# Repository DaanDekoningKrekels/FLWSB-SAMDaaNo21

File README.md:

# Flexible LoRaWAN Sensor Board SAMDaaNo21

Het FLWSB Main Board is een microcontroller bord gebaseerd op de ATSAM D21 in de vormfactor vergelijkbaar met een Arduino Nano. Het moet gemakkelijk zijn om dit bord in een breadboard te prikken en zo testen uit te voeren of schakelingen te bouwen. 

[PDF versie van de pinout diagram](./assets/SAMDaaNo21-pinout.pdf ':ignore')

## KiCad bibliotheken

Het is handig om een printplaat te kunnen ontwikkelen waar de SAMDaaNo21 opgeprikt kan worden.

Om dit proces te vergemakkelijken is er een KiCad bibliotheek ontwikkeld, die bevat een symbol, footprint en 3D-model.

Het is aangeraden om bibliotheken die niet standaard in KiCad zitten mee in de projectmap te steken en te importeren als projectbibliotheek. Als je je projectmap dan deelt met derden zullen zij meteen beschikken over alle nodige bibliotheken.

Tutorial: [How to import into KiCad V6 & later?](https://support.snapeda.com/en/articles/5995733-how-to-import-into-kicad-v6-later)

[SAMDaaNo21 bibliotheek bestanden](https://github.com/Dacetylan/FLWSB/tree/SAMDaaNo21/src/printed-circuit-boards/FLWSB-SAMDaaNo21-KiCad-lib)

## Schema

Het elektrisch schema van dit bord ziet er als volgt uit:

Alle onderdelen worden verder toegelicht.

[ATSAM D21 Datasheet](https://ww1.microchip.com/downloads/en/DeviceDoc/SAM-D21DA1-Family-Data-Sheet-DS40001882G.pdf)

## Testpunten

Er zijn verschillende testpunten toegevoegd om op een gemakkelijke en toegankelijke manier verschillende parameters op het bord te kunnen meten.

Er is gekozen voor through hole testpunten zodat het gemakkelijk is om deze met een probe te meten. Alle testpunten zijn te vinden nabij de USB poort.

| Testpunt nummer | Verbinding                                                   |
| --------------- | ------------------------------------------------------------ |
| TP1             | VBUS: 5 V afkomstig van USB                                  |
| TP2             | VDD: 3,3 V gereguleerde spanning                              |
| TP3             | VIN: Ingangsspanning voordat het naar de lineaire regelaar gaat |

## LoRaWAN Module

Er is een RN2483 module mee geïmplementeerd op de printplaat. Deze is aangesloten op de UART bus van SERCOM 2.

De RN2483 bevindt zich aan het uiteinde. Er kan een antenne aangesloten worden via een U.FL connector.  

[Productpagina connector](https://be.farnell.com/hirose-hrs/u-fl-r-smt-1-10/rf-coaxial-u-fl-straight-jack/dp/1688077)

## USB Interface & VIN

Het schema voor de USB-interface is gebaseerd op een voorbeeld uit een Atmel handleiding. De zener diodes die zichtbaar zijn zorgen ervoor dat de kans op schade door elektrostatische ontlading (ESD) beperkt wordt.

[Ref USB-applications note](https://ww1.microchip.com/downloads/en/DeviceDoc/Atmel-42261-SAM-D21-USB_Application-Note_AT06475.pdf)

[Ref schematic checklist](https://ww1.microchip.com/downloads/en/DeviceDoc/SAM-D21DA1-Family-Data-Sheet-DS40001882G.pdf#_OPENTOPIC_TOC_PROCESSING_d10240e380866)

De Schottky diode (D6) is er om de USB-poort van je laptop te beschermen wanneer het bord van stroom wordt voorzien via de VIN pin. Het zou kunnen dat aan de VIN pin een hogere spanning wordt geleverd dan 5 V waardoor dit potentiaalverschil ongewenste stroom kan laten vloeien. Hetzelfde principe wordt toegepast bij de ESP32 DEVKIT.

`TP3` is een testpunt dat aanwezig is om op een toegankelijke manier de VIN-spanning te meten.

[Ref ESP32 schema](https://dl.espressif.com/dl/schematics/esp32_devkitc_v4-sch-20180607a.pdf)

Het bordje kan voorzien worden van stroom via de USB-C poort. Een LDO (Low Dropout regelaar) zal de spanning afkomstig van de computer reguleren naar een stabiele 3,3 V.

De LDO is een LD1117S33 en ondersteunt een minimale ingangsspanning van 4,3 V en een maximale van 15 V. Dat kan worden aangelegd via de VIN pin. Er is een Schottky diode voorzien om ervoor te zorgen dat de spanning van VIN niet op de USB poort komt te staan.

*Let op dat je met een lineaire regelaar te maken hebt. Hoe hoger de ingangsspanning, hoe warmer de LDO zal worden!*

Het is ook mogelijk om de regelaar over te slaan en rechtstreeks 3,3 V te leveren via de 3V3 pin. Dit kan handig zijn bij een situatie waarin we zo zuinig mogelijk willen zijn en een efficiëntere 3,3 V regelaar gebruiken van een andere pcb. *Belangrijk is dat deze spanning niet te hard mag afwijken van 3,3 V!*

## RESET & DEBUG

De reset knop is opgebouwd zoals in de datasheet van de ATSAM D21 wordt weergegeven onder "Schematic Checklist Figure 45-4. External Reset Circuit Schematic".

Als er nog geen bootloader op de ATSAMD staat of als we een bare metal installatie gebruiken zullen we gebruik moeten maken van de program en debug header. Dat zijn de 3 pinnen centraal op de printplaat voor de LoRaWAN module. De pinout van links naar recht is: RESET, SWDIO, SWCLK. 

De ATSAMD maakt gebruik van Serial Wire Debugging (SWD), dat maakt het mogelijk om via fuses in te stellen, binaries in te laden en zelfs break-points aan je code toe te voegen.

## Low Dropout Lineair Regulator

In dit geval wordt er een LD1117 3,3 V regelaar gebruikt. Deze regelaar kan met een vrij groot ingangsbereik (tot 15 V) een uitgangsspanning van 3,3 V leveren.

`TP2` is een testpunt dat aanwezig is om op een toegankelijke manier de 3.3 V gereguleerde spanning te meten.

[LD1117 datasheet](https://www.st.com/resource/en/datasheet/ld1117.pdf)

## Power Supply Connections

Het schema voor de ontkoppelcondensatoren en spoel voor de ATSAM D21 komt ook rechtstreeks uit de datasheet. Wat belangrijk is bij deze componenten is dat alles rechts van de blauwe stippellijn zo dicht mogelijk bij de vermelde pinnen staat. Deze condensatoren vangen kleine storingen en rimpels op die zich voordoen in de bronspanning.

## Input / Output

Dit zijn alle GPIO, SERCOM en power aansluitingen die via pinheaders naar buiten worden gebracht. De SERCOM poorten zijn alvast gedefinieerd zodat onder andere de pull-up weerstanden geplaatst kunnen worden. Alle andere poorten zijn voor algemeen gebruik. In de datasheet van de ATSAM D21 onder 7. I/O Multiplexing and Considerations kunnen alle verschillende mogelijkheden van deze aansluitingen gevonden worden (AC, ADC, DAC, PTC, DAC, IO, ...).

PA12 en PA13 zijn onderdeel van de I²C bus en hebben al een pull-up weerstand van 4,7 K voorzien. *Bij het plaatsen van nog externe pull-up weerstanden zullen zij in parallel staan en zal de weerstandswaarde te laag worden.*

| I/O Pin | Pin      | SERCOM                  | SERCOM-ALT       | External Interrupt | ADC, DAC, AC, REF    | Peripheral Touch Controller | TC/TCC         | TCC            | COM               | Generic Clock Generator |
| ------- | -------- | ----------------------- | ---------------- | ------------------ | -------------------- | --------------------------- | -------------- | -------------- | ----------------- | ----------------------- |
| GND     | PowerPin | Ground Reference        |                  |                    |                      |                             |                |                |                   |                         |
| PA02    | 3        |                         |                  | EXTINT:2           | ADC:0<br/>VOUT       | Y:0                         |                | TCC3/<br/>WO:0 |                   |                         |
| PA03    | 4        |                         |                  | EXTINT:3           | ADC:1<br/>VREFA      | Y:1                         |                | TCC3/<br/>WO:1 |                   |                         |
| PB08    | 7        |                         | SCOM4/<br/>PAD:0 | EXTINT:8           | ADC:2                | Y:14                        | TC4/<br/>WO:0  | TCC3/<br/>WO:6 |                   |                         |
| PB09    | 8        |                         | SCOM4/<br/>PAD:1 | EXTINT:9           | ADC:3                | Y:15                        | TC4/<br/>WO:1  | TCC3/<br/>WO:7 |                   |                         |
| PA04    | 9        |                         | SCOM0/<br/>PAD:0 | EXTINT:4           | ADC:4<br/>AC:0 VREFB | Y:2                         | TCC0/<br/>WO:0 | TCC3/<br/>WO:2 |                   |                         |
| PA05    | 10       |                         | SCOM0/<br/>PAD:1 | EXTINT:5           | ADC:5<br/>AC:1       | Y:3                         | TCC0/<br/>WO:1 | TCC3/<br/>WO:3 |                   |                         |
| PA06    | 11       |                         | SCOM0/<br/>PAD:2 | EXTINT:6           | ADC:6<br/>AC:2       | Y:4                         | TCC1/<br/>WO:0 | TCC3/<br/>WO:4 |                   |                         |
| PA07    | 12       |                         | SCOM0/<br/>PAD:3 | EXTINT:7           | ADC:7<br/>AC:3       | Y:5                         | TCC1/<br/>WO:1 | TCC3/<br/>WO:5 | I2S/<br/>SD:0     |                         |
| PA08    | 13       | SCOM0/<br/>PAD:0        | SCOM2/<br/>PAD:0 | NMI                | ADC:16               | X:0                         | TCC0/<br/>WO:0 | TCC1/<br/>WO:2 | I2S/<br/>SD:1     |                         |
| PA09    | 14       | SCOM0/<br/>PAD:1        | SCOM2/<br/>PAD:1 | EXTINT:9           | ADC:17               | X:1                         | TCC0/<br/>WO:1 | TCC1/<br/>WO:3 | I2S/<br/>MCK:0    |                         |
| PA10    | 15       | SCOM0/<br/>PAD:2        | SCOM2/<br/>PAD:2 | EXTINT:10          | ADC:18               | X:2                         | TCC1/<br/>WO:0 | TCC0/<br/>WO:2 | I2S/<br/>SCK:0    | GCLK:4                  |
| PA11    | 16       | SCOM0/<br/>PAD:3        | SCOM2/<br/>PAD:3 | EXTINT:11          | ADC:19               | X:3                         | TCC1/<br/>WO:1 | TCC0/<br/>WO:3 | I2S/<br/>FS:0     | GCLK:5                  |
| PA12    | 21       | SCOM2/<br/>PAD:0        | SCOM4/<br/>PAD:0 | EXTINT:12          | AC:0                 |                             | TCC2/<br/>WO:0 | TCC0/<br/>WO:6 |                   |                         |
| PA13    | 22       | SCOM2/<br/>PAD:1        | SCOM4/<br/>PAD:1 | EXTINT:13          | AC:1                 |                             | TCC2/<br/>WO:1 | TCC0/<br/>WO:7 |                   |                         |
| VIN     | PowerPin | LDL1117S33 4.3 V - 15 V |                  |                    |                      |                             |                |                |                   |                         |
| 3V3     | PowerPin | 3.3V LDO output         |                  |                    |                      |                             |                |                |                   |                         |
| GND     | PowerPin | Ground Reference        |                  |                    |                      |                             |                |                |                   |                         |
| PB03    | 48       |                         | SCOM5/<br/>PAD:1 | EXTINT:3           | ADC:11               | Y:9                         | TC6/<br/>WO:1  | TCC3/<br/>WO:3 |                   |                         |
| PB22    | 37       |                         | SCOM5/<br/>PAD:2 | EXTINT:6           |                      |                             | TC7/<br/>WO:0  | TCC3/<br/>WO:0 |                   | GCLK:0                  |
| PA23    | 32       | SCOM3/<br/>PAD:1        | SCOM5/<br/>PAD:1 | EXTINT:7           |                      | X:11                        | TC4/<br/>WO:0  | TCC0/<br/>WO:5 | USB/<br/>SOF 1KhZ | GCLK:7                  |
| PA22    | 31       | SCOM3/<br/>PAD:0        | SCOM5/<br/>PAD:0 | EXTINT:6           |                      | X:10                        | TC4/<br/>WO:1  | TCC0/<br/>WO:4 |                   | GCLK:6                  |
| PA21    | 30       | SCOM5/<br/>PAD:3        | SCOM3/<br/>PAD:3 | EXTINT:5           |                      | X:9                         | TC7/<br/>WO:1  | TCC0/<br/>WO:7 | I2S/<br/>FS:0     | GCLK:5                  |
| PA20    | 29       | SCOM5/<br/>PAD:2        | SCOM3/<br/>PAD:2 | EXTINT:4           |                      | X:8                         | TC7/<br/>WO:0  | TCC0/<br/>WO:6 | I2S/<br/>SCK:0    | GCLK:4                  |
| PA19    | 28       | SCOM1/<br/>PAD:3        | SCOM3/<br/>PAD:3 | EXTINT:3           | AC:1                 | X:7                         | TC3/<br/>WO:1  | TCC0/<br/>WO:3 | I2S/<br/>SD:0     |                         |
| PA18    | 27       | SCOM1/<br/>PAD:2        | SCOM3/<br/>PAD:2 | EXTINT:2           | AC:0                 | X:6                         | TC3/<br/>WO:0  | TCC0/<br/>WO:2 |                   |                         |
| PA17    | 26       | SCOM1/<br/>PAD:1        | SCOM3/<br/>PAD:1 | EXTINT:1           |                      | X:5                         | TCC2/<br/>WO:1 | TCC0/<br/>WO:7 |                   | GCLK:3                  |
| PA16    | 25       | SCOM1/<br/>PAD:0        | SCOM3/<br/>PAD:0 | EXTINT:0           |                      | X:4                         | TCC2/<br/>WO:0 | TCC0/<br/>WO:6 |                   | GCLK:2                  |
| PA15    | 24       | SCOM2/<br/>PAD:3        | SCOM4/<br/>PAD:3 | EXTINT:15          |                      |                             | TC3/<br/>WO:1  | TCC0/<br/>WO:5 |                   | GCLK:1                  |
| PA14    | 23       | SCOM2/<br/>PAD:2        | SCOM4/<br/>PAD:2 | EXTINT:14          |                      |                             | TC3/<br/>WO:0  | TCC0/<br/>WO:4 |                   | GCLK:0                  |

### Legende

`SERCOM`: Serial Communication, keuze tussen: USART, I²C, SPI of SMBus

`EXTINT[n]`: External Interrupts

`AIN[n]`: ADC Analog Inputs

`X[n]`, `Y[n]`: Peripheral Touch Controller - PTC Input

`TC4/WO[n]`, `TC6/WO[n]`: Waveform/PWM Outputs

`TCC3/WO[n]`: Waveform/PWM Outputs/ Capture Inputs

`AC/CMP[n]`: AC Comparator Outputs

`I2S/FS[n]`: Inter-IC Sound Controller, I²S Word Select or TDM Frame Sync

`GCLK_IO[n]`: Generic Clock (source clock or generic clock generator output)

## Toekomstige verbeteringen

- Momenteel zijn er geen mounting holes aanwezig, dat vonden we  nog niet prioritair.
  - Mouning holes of inkepingen aan de randen van de printplaat zijn dus nog mogelijk en kunnen ook zeker van pas komen.
- De impedantie van het pad naar de antenne-aansluiting is niet theoretisch berekend. Dit is iets waar in een volgende versie over kan worden nagedacht.
- Er is geen LED aanwezig.
- Op het silkscreen staat een fout, `PA07` staat op het silkscreen als `PA09`. 
- Het schema bevat een fout die de LoRaWAN module onbruikbaar maakt. RX en TX van de UART-verbinding moeten omgewisseld worden.
  
### Tijdelijke oplossing LoRaWAN module

Een UART-verbinding heeft een TX (transmit) en RX (receive) aansluiting nodig. Logischerwijze zal je dus, bij een verbinding tussen twee apparaten, RX en TX met elkaar verbinden. Bij het ontwerpen van dit schema is door onoplettendheid TX met TX verbonden en RX met RX verbonden.

De PINMUX van de ATSAM D21 kan iedere SERCOM pin als RX instellen, maar niet iedere pin als TX schakelen. Dit maakt het onmogelijk om de oplossing geheel softwarematig te zoeken. Enkel PAD0 en PAD2 van een SERCOM poort kan je instellen als TX.

Wij hebben `PA8` (`S2TX` op het silkscreen) ingesteld als RX omdat deze verbonden is met de TX van de LoRaWAN module. `PA09` (`S2RX` op het silkscreen) hebben we hoog impedant gezet (`INPUT`) en kortgesloten met `PA10`. `PA10` is PAD2 van SERCOM2 dus kan ingesteld worden als nieuwe TX.

Het resultaat is dat we nu het baantje naar de RESET pin van de LoRaWAN module moeten onderbreken, omdat `PA10` verbonden is met deze pin. Die onderbreking is het gemakkelijkste te maken met een mesje of platte schroevendraaier net op de plek waar deze richting het pad van de module gaat.

De aanpassingen van deze pinnen is gemaakt in de ArduinoCore dus er hoeft in de code niets gewijzigd te worden.

Er is geen manier meer om de module te resetten vanaf de MCU, moest dat nodig zijn, dan kan er een kabeltje gesoldeerd worden naar een van de vrije GPIO pinnen.

## Bill of Materials

[Bill of materials ibom](./bom/ibom.html ':include :type=iframe width=100% height=1024px')

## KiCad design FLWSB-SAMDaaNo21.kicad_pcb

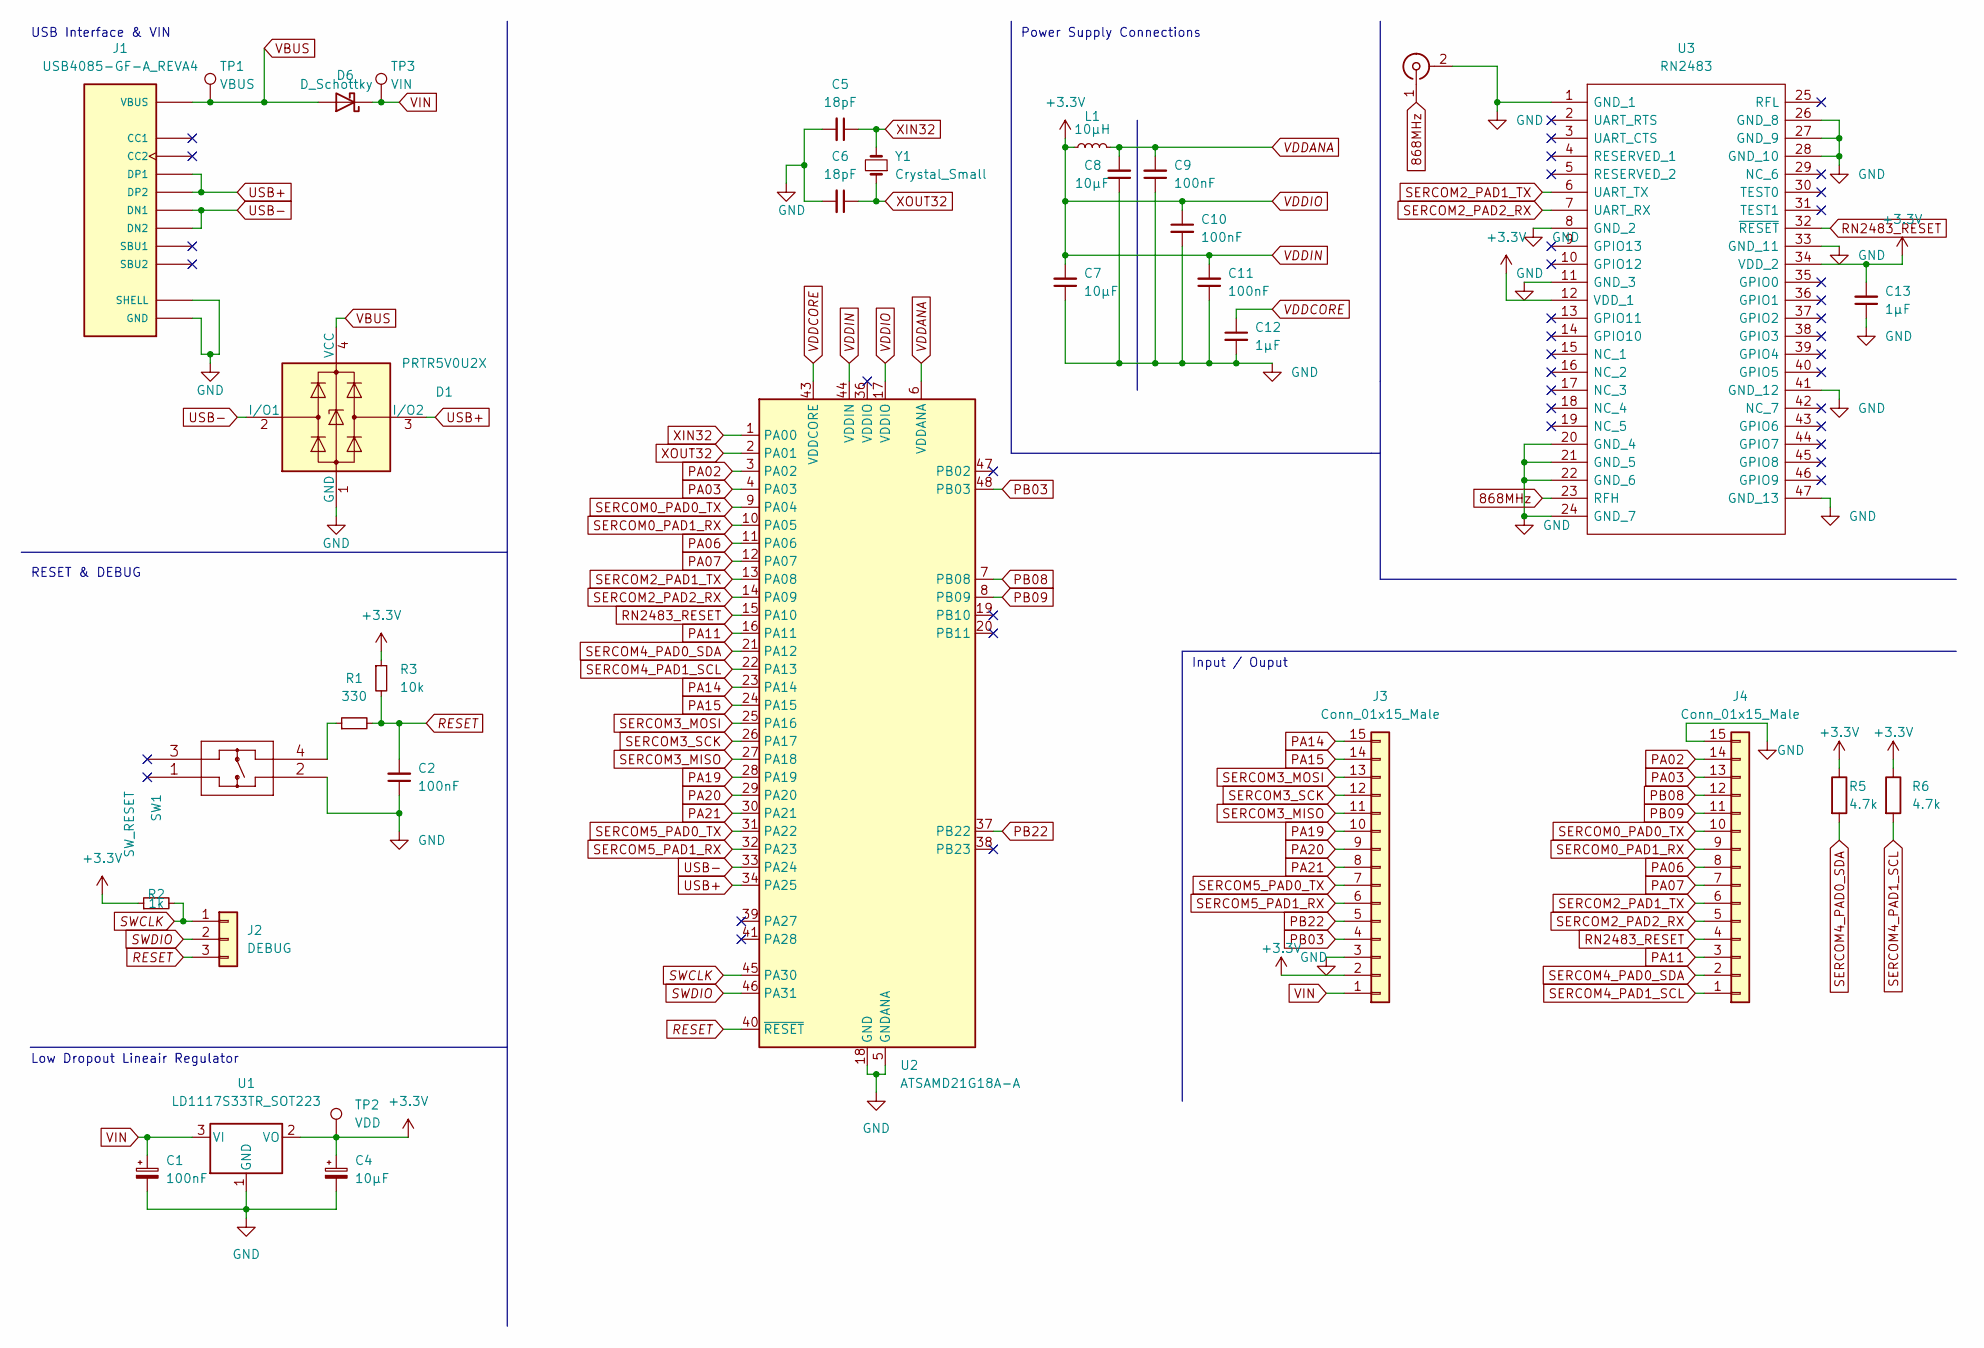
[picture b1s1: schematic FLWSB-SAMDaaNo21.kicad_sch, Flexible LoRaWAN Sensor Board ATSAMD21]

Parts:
C1, C2, C9, C10, C11: 100nF; C_0805_2012Metric_Pad1.18x1.45mm_HandSolder
C4, C7, C8: 10µF; C_0805_2012Metric_Pad1.18x1.45mm_HandSolder
C5, C6: 18pF; C_0805_2012Metric_Pad1.18x1.45mm_HandSolder
C12, C13: 1µF; C_0805_2012Metric_Pad1.18x1.45mm_HandSolder
D1: PRTR5V0U2X; SOT-143
D6: D_Schottky; SOD-123FL
J1: USB4085-GF-A_REVA4; GCT_USB4085-GF-A_REVA4; PARTREV A4
J2: DEBUG; PinHeader_1x03_P2.54mm_Vertical
J3, J4: Conn_01x15_Male; PinHeader_1x15_P2.54mm_Vertical
J6: Conn_Coaxial; U.FL_Molex_MCRF_73412-0110_Vertical
L1: 10µH; L_Murata_LQH2MCNxxxx02_2.0x1.6mm
R1: 330; R_0805_2012Metric_Pad1.20x1.40mm_HandSolder
R2: 1k; R_0805_2012Metric_Pad1.20x1.40mm_HandSolder
R3: 10k; R_0805_2012Metric_Pad1.20x1.40mm_HandSolder
R5, R6: 4.7k; R_0805_2012Metric_Pad1.20x1.40mm_HandSolder
SW1: SW_RESET; KMR7_CNK
TP1: VBUS; TestPoint_THTPad_1.0x1.0mm_Drill0.5mm
TP2: VDD; TestPoint_THTPad_1.0x1.0mm_Drill0.5mm
TP3: VIN; TestPoint_THTPad_1.0x1.0mm_Drill0.5mm
U1: LD1117S33TR_SOT223; SOT-223-3_TabPin2
U2: ATSAMD21G18A-A; TQFP-48_7x7mm_P0.5mm
U3: RN2483; Manufacturer_Part_Number RN2483
Y1: Crystal_Small; Crystal_SMD_3215-2Pin_3.2x1.5mm

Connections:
868MHz: J6.1 (In), U3.23 (RFH)
GND: C1.2, C2.1, C4.2, C5.2, C6.2, C7.1, C8.1, C9.1, C10.2, C11.1, C12.2, C13.1, D1.1 (GND), J1.A1 (GND), J1.A12 (GND), J1.B1 (GND), J1.B12 (GND), J1.P1 (SHELL), J1.P2 (SHELL), J1.P3 (SHELL), J1.P4 (SHELL), J3.3, J4.15, J6.2 (Ext), SW1.2, U1.1 (GND), U2.5 (GNDANA), U2.18 (GND), U2.35 (GND), U2.42 (GND), U3.1 (GND_1), U3.8 (GND_2), U3.11 (GND_3), U3.20 (GND_4), U3.21 (GND_5), U3.22 (GND_6), U3.24 (GND_7), U3.26 (GND_8), U3.27 (GND_9), U3.28 (GND_10), U3.33 (GND_11), U3.41 (GND_12), U3.47 (GND_13); also elsewhere on the board
unnamed: R1.1, SW1.4
PA02: J4.14, U2.3 (PA02)
PA03: J4.13, U2.4 (PA03)
PA06: J4.8, U2.11 (PA06)
PA07: J4.7, U2.12 (PA07)
PA11: J4.3, U2.16 (PA11)
PA14: J3.15, U2.23 (PA14)
PA15: J3.14, U2.24 (PA15)
PA19: J3.10, U2.28 (PA19)
PA20: J3.9, U2.29 (PA20)
PA21: J3.8, U2.30 (PA21)
PB03: J3.4, U2.48 (PB03)
PB08: J4.12, U2.7 (PB08)
PB09: J4.11, U2.8 (PB09)
PB22: J3.5, U2.37 (PB22)
RESET: C2.2, J2.3, R1.2, R3.2, U2.40 (~RESET)
RN2483_RESET: J4.4, U2.15 (PA10), U3.32 (~RESET)
SERCOM0_PAD0_TX: J4.10, U2.9 (PA04)
SERCOM0_PAD1_RX: J4.9, U2.10 (PA05)
SERCOM2_PAD1_TX: J4.6, U2.13 (PA08), U3.6 (UART_TX)
SERCOM2_PAD2_RX: J4.5, U2.14 (PA09), U3.7 (UART_RX)
SERCOM3_MISO: J3.11, U2.27 (PA18)
SERCOM3_MOSI: J3.13, U2.25 (PA16)
SERCOM3_SCK: J3.12, U2.26 (PA17)
SERCOM4_PAD0_SDA: J4.2, R5.2, U2.21 (PA12)
SERCOM4_PAD1_SCL: J4.1, R6.2, U2.22 (PA13)
SERCOM5_PAD0_TX: J3.7, U2.31 (PA22)
SERCOM5_PAD1_RX: J3.6, U2.32 (PA23)
SWCLK: J2.1, R2.2, U2.45 (PA30)
SWDIO: J2.2, U2.46 (PA31)
USB+: D1.3 (I/O2), J1.A6 (DP1), J1.B6 (DP2), U2.34 (PA25)
USB-: D1.2 (I/O1), J1.A7 (DN1), J1.B7 (DN2), U2.33 (PA24)
VBUS: D1.4 (VCC), D6.2 (A), J1.A4 (VBUS), J1.A9 (VBUS), J1.B4 (VBUS), J1.B9 (VBUS), TP1.1
VDDANA: C8.2, C9.2, L1.2, U2.6 (VDDANA)
VDDCORE: C12.1, U2.43 (VDDCORE)
VDDIN: C4.1, C7.2, C10.1, C11.2, C13.2, J3.2, L1.1, R2.1, R3.1, R5.1, R6.1, TP2.1, U1.2 (VO), U2.17 (VDDIO), U2.44 (VDDIN), U3.12 (VDD_1), U3.34 (VDD_2)
VIN: C1.1, D6.1 (K), J3.1, TP3.1, U1.3 (VI)
XIN32: C5.1, U2.1 (PA00), Y1.2; also elsewhere on the board
XOUT32: C6.1, U2.2 (PA01), Y1.1

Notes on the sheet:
Power Supply Connections
Input / Ouput
Low Dropout Lineair Regulator
RESET & DEBUG
USB Interface & VIN

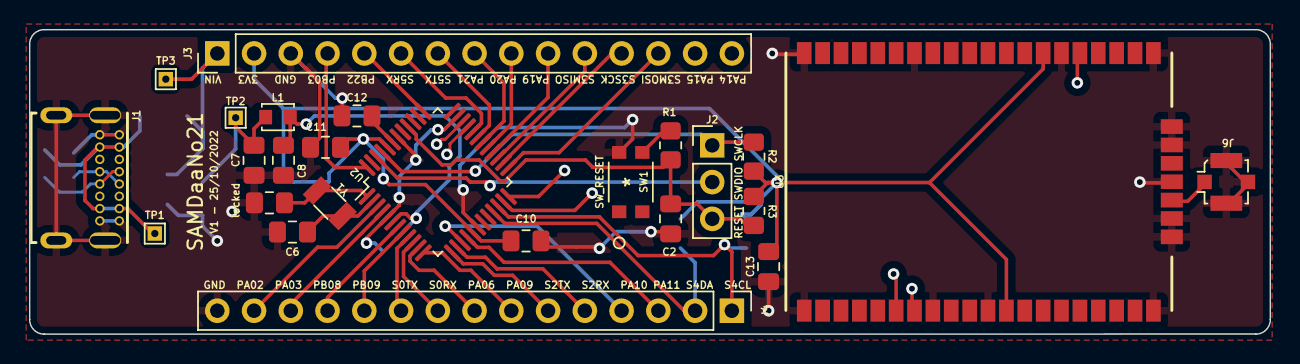
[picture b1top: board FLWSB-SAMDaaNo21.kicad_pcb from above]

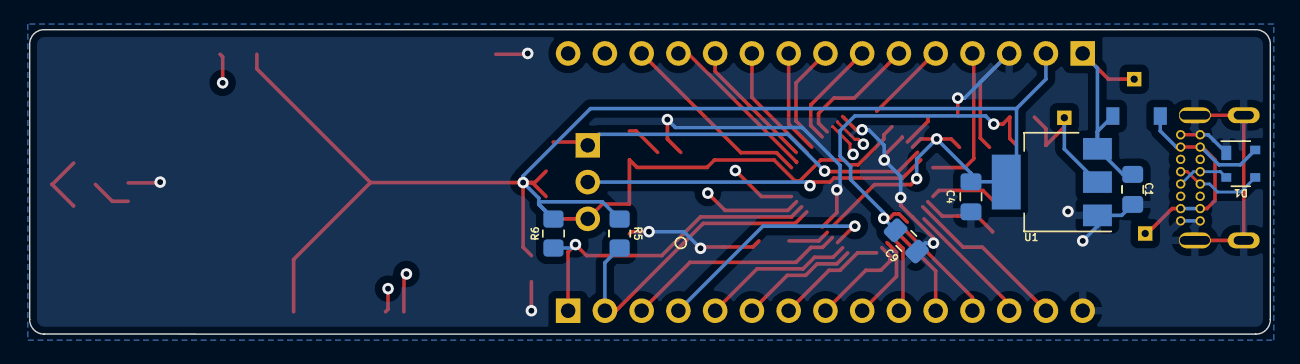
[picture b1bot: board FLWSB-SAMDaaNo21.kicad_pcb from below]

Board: 4 copper layers, 85.7 x 21.0 mm, 33 parts (8 on the bottom side), 41 nets.

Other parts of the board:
locked: 18pF; C_0805_2012Metric_Pad1.18x1.45mm_HandSolder

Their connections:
GND: locked.2; also elsewhere on the board
XIN32: locked.1; also elsewhere on the board

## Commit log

2022-09-23 Basis SAMDaaNo21 bord
2022-09-23 Update afbeelding pad
2022-09-30 Schema zo goed als af
2022-10-07 PCB bijna af
2022-10-25 Laatste verbeteringen
2022-10-28 USB-C shell aan GND ipv R en C
2022-10-28 finale versie
2022-10-28 BOM in docs
2023-01-18 update documentatie en aanpassing blokdiagram
2023-01-18 Finishing touches

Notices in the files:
parts and their libraries:
Copyright 2021 Accelerated Designs. All rights reserved.
